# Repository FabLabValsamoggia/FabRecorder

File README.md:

# FabRecorder

developed with ♥ by FabLab Valsamoggia

Based on [this awesome project](https://www.instructables.com/id/Make-Your-Own-Spy-Bug-Arduino-Voice-Recorder/).

**FabRecorder** is a little and adorable object, inspired by 007 gadget, that permits to record audio .wav format on SD card.

## Installation

Library requirements: [TMRpcm](https://github.com/TMRh20/TMRpcm). See code for other informations.

## Contributing

Pull requests are welcome. For major changes, please open an issue first to discuss what you would like to change.

Please make sure to update tests as appropriate.

## License

[MIT](https://choosealicense.com/licenses/mit/)

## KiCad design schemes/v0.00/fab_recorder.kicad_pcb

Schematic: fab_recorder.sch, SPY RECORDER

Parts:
J101, J102: Conn_01x12_Female; PinSocket_1x12_P2.54mm_Vertical_SMD_Pin1Left
R101: 4K7; R_0805_2012Metric_Pad1.15x1.40mm_HandSolder
SW101: SW_Push; SW_SPST_TL3305A

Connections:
/0(Rx): J101.2
/1(Tx): J101.1
/2: J101.5
/3(**): J101.6
/4: J101.7, R101.1, SW101.2
/5(**): J101.8
/6(**): J101.9
/7: J101.10
/8: J101.11
/9(**): J101.12
/10(**/SS): J102.12; also elsewhere on the board
/11(**/MOSI): J102.11; also elsewhere on the board
/12(MISO): J102.10; also elsewhere on the board
/13(SCK): J102.9; also elsewhere on the board
/A0: J102.8; also elsewhere on the board
/A1: J102.7
/A2: J102.6
/A3: J102.5
/RAW: J102.1
/Reset: J101.3
/Reset2: J102.3
GND: J101.4, J102.2, R101.2; also elsewhere on the board
VCC: J102.4, SW101.1; also elsewhere on the board

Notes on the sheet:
Shield Arduino Pro Mini

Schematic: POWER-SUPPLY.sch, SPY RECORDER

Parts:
C201, C203: 10uF S; C_0805_2012Metric_Pad1.15x1.40mm_HandSolder
C202: 100nF S; C_0805_2012Metric_Pad1.15x1.40mm_HandSolder
D201: RED; LED_0805_2012Metric
D202: GREEN; LED_0805_2012Metric
J201: USB_B_Micro; USB_Micro-B_Molex_47346-0001
J202: Conn_01x02_Female; Molex_PicoBlade_53048-0210_1x02_P1.25mm_Horizontal
R201: 2K S; R_0805_2012Metric_Pad1.15x1.40mm_HandSolder
R202, R203: 470R S; R_0805_2012Metric_Pad1.15x1.40mm_HandSolder
U201: MCP73831-2-OT; SOT-23-5
U202: LP2981-33DBVT; SOT-23-5_HandSoldering; Mouser Part Number 595-LP2981-33DBVT

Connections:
/POWER SUPPLY/VBATT: C201.1, C202.1, J202.1, U201.3, U202.1 (VIN), U202.3 (ON/~OFF)
GND: C201.2, C202.2, C203.2, D202.1, J201.5, J202.2, R201.2, U201.2, U202.2 (GND); also elsewhere on the board
unnamed: D201.1, R203.2, U201.1
unnamed: D201.2, R202.2
unnamed: D202.2, R203.1
unnamed: J201.1, R202.1, U201.4
unnamed: R201.1, U201.5
VCC: C203.1, U202.5 (VOUT); also elsewhere on the board

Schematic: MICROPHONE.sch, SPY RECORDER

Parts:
C301, C302: 4.7uF S; C_0805_2012Metric_Pad1.15x1.40mm_HandSolder
C303: 100nF S; C_0805_2012Metric_Pad1.15x1.40mm_HandSolder
MK301: Microphone; MIC_CMA-4544PF-W
R301: 2.2K S; R_0805_2012Metric_Pad1.15x1.40mm_HandSolder
R302, R303, R304: 10K S; R_0805_2012Metric_Pad1.15x1.40mm_HandSolder
R305: 820K S; R_0805_2012Metric_Pad1.15x1.40mm_HandSolder
U301: OPA334; SOT-23-5_HandSoldering

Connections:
/A0: R305.1, U301.1; also elsewhere on the board
GND: C302.2, C303.2, MK301.1, R304.1, U301.2 (V-); also elsewhere on the board
unnamed: C301.1, R302.2
unnamed: C301.2, MK301.2, R301.2
unnamed: C302.1, R303.1, R304.2, U301.3 (+)
unnamed: R302.1, R305.2, U301.4 (-)
VCC: C303.1, R301.1, R303.2, U301.5 (V+); also elsewhere on the board

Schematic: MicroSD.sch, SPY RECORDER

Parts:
D401: RED; LED_0805_2012Metric
J401: Micro_SD_Card; microSD_HC_Molex_104031-0811
R401: 470; R_0805_2012Metric_Pad1.15x1.40mm_HandSolder
U401: CD74HC4050M; SOP-16_4.55x10.3mm_P1.27mm

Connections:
/10(**/SS): U401.7 (3A), U401.14 (6A); also elsewhere on the board
/11(**/MOSI): U401.5 (2A); also elsewhere on the board
/12(MISO): J401.7; also elsewhere on the board
/13(SCK): U401.3 (1A); also elsewhere on the board
GND: J401.6, U401.8 (GND); also elsewhere on the board
unnamed: D401.1, J401.2, U401.2 (1Y)
unnamed: D401.2, R401.2
unnamed: J401.3, U401.4 (2Y)
unnamed: J401.5, U401.6 (3Y)
unnamed: R401.1, U401.15 (6Y)
VCC: J401.4, U401.1 (VCC); also elsewhere on the board

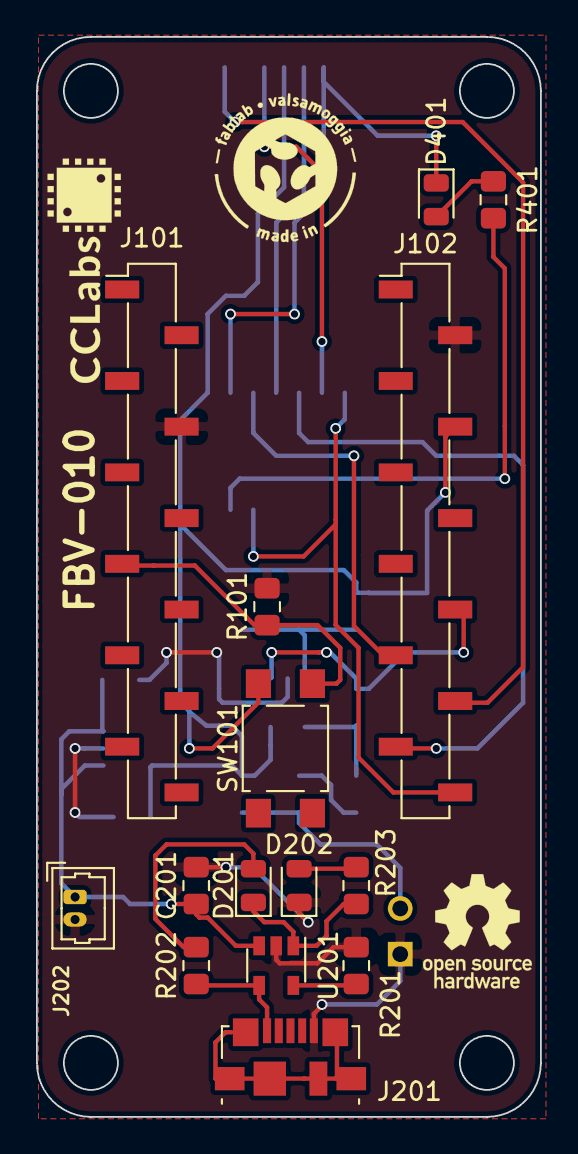
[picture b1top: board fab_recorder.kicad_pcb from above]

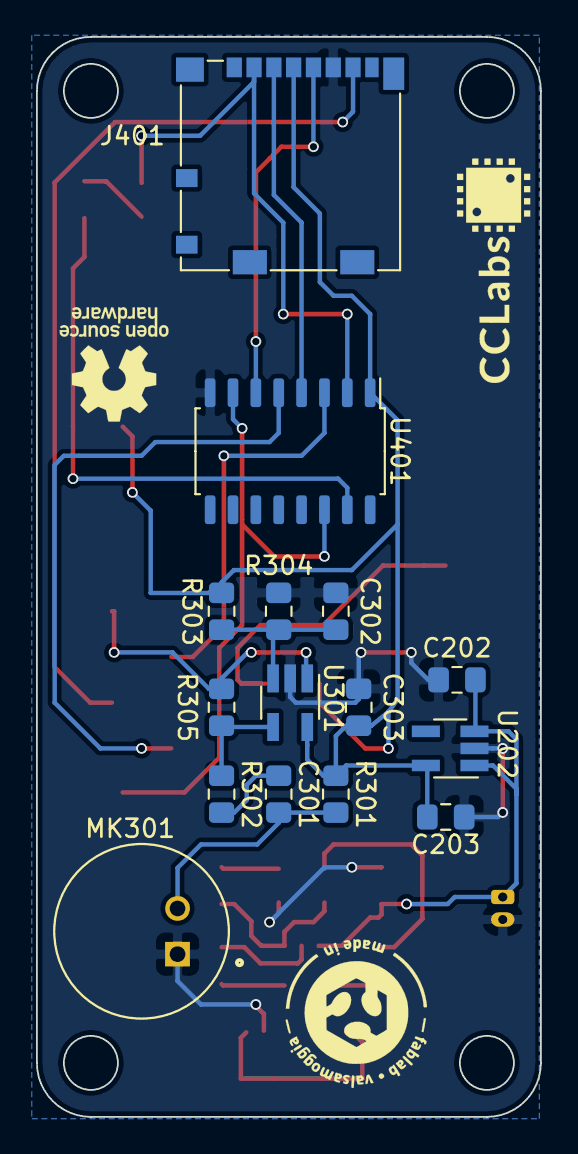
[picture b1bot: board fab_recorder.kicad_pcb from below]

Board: 2 copper layers, 28.0 x 60.0 mm, 30 parts (15 on the bottom side), 23 nets.
